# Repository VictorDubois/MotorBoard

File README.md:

Custom PCB, used by KrabiV2.

Drives two brushless motors C610/M2006, controlled with dedicated encoders wheels, and 4 simple transistor outputs.

Driven by a [STM32 NUCLEO-G431KB](https://www.st.com/en/evaluation-tools/nucleo-g431kb.html)

[The code is here](https://github.com/VictorDubois/Motor-board-STM32-CAN)

[Click for online viewer<br/>

](https://kicanvas.org/?repo=https%3A%2F%2Fgithub.com%2FVictorDubois%2FMotorBoard)

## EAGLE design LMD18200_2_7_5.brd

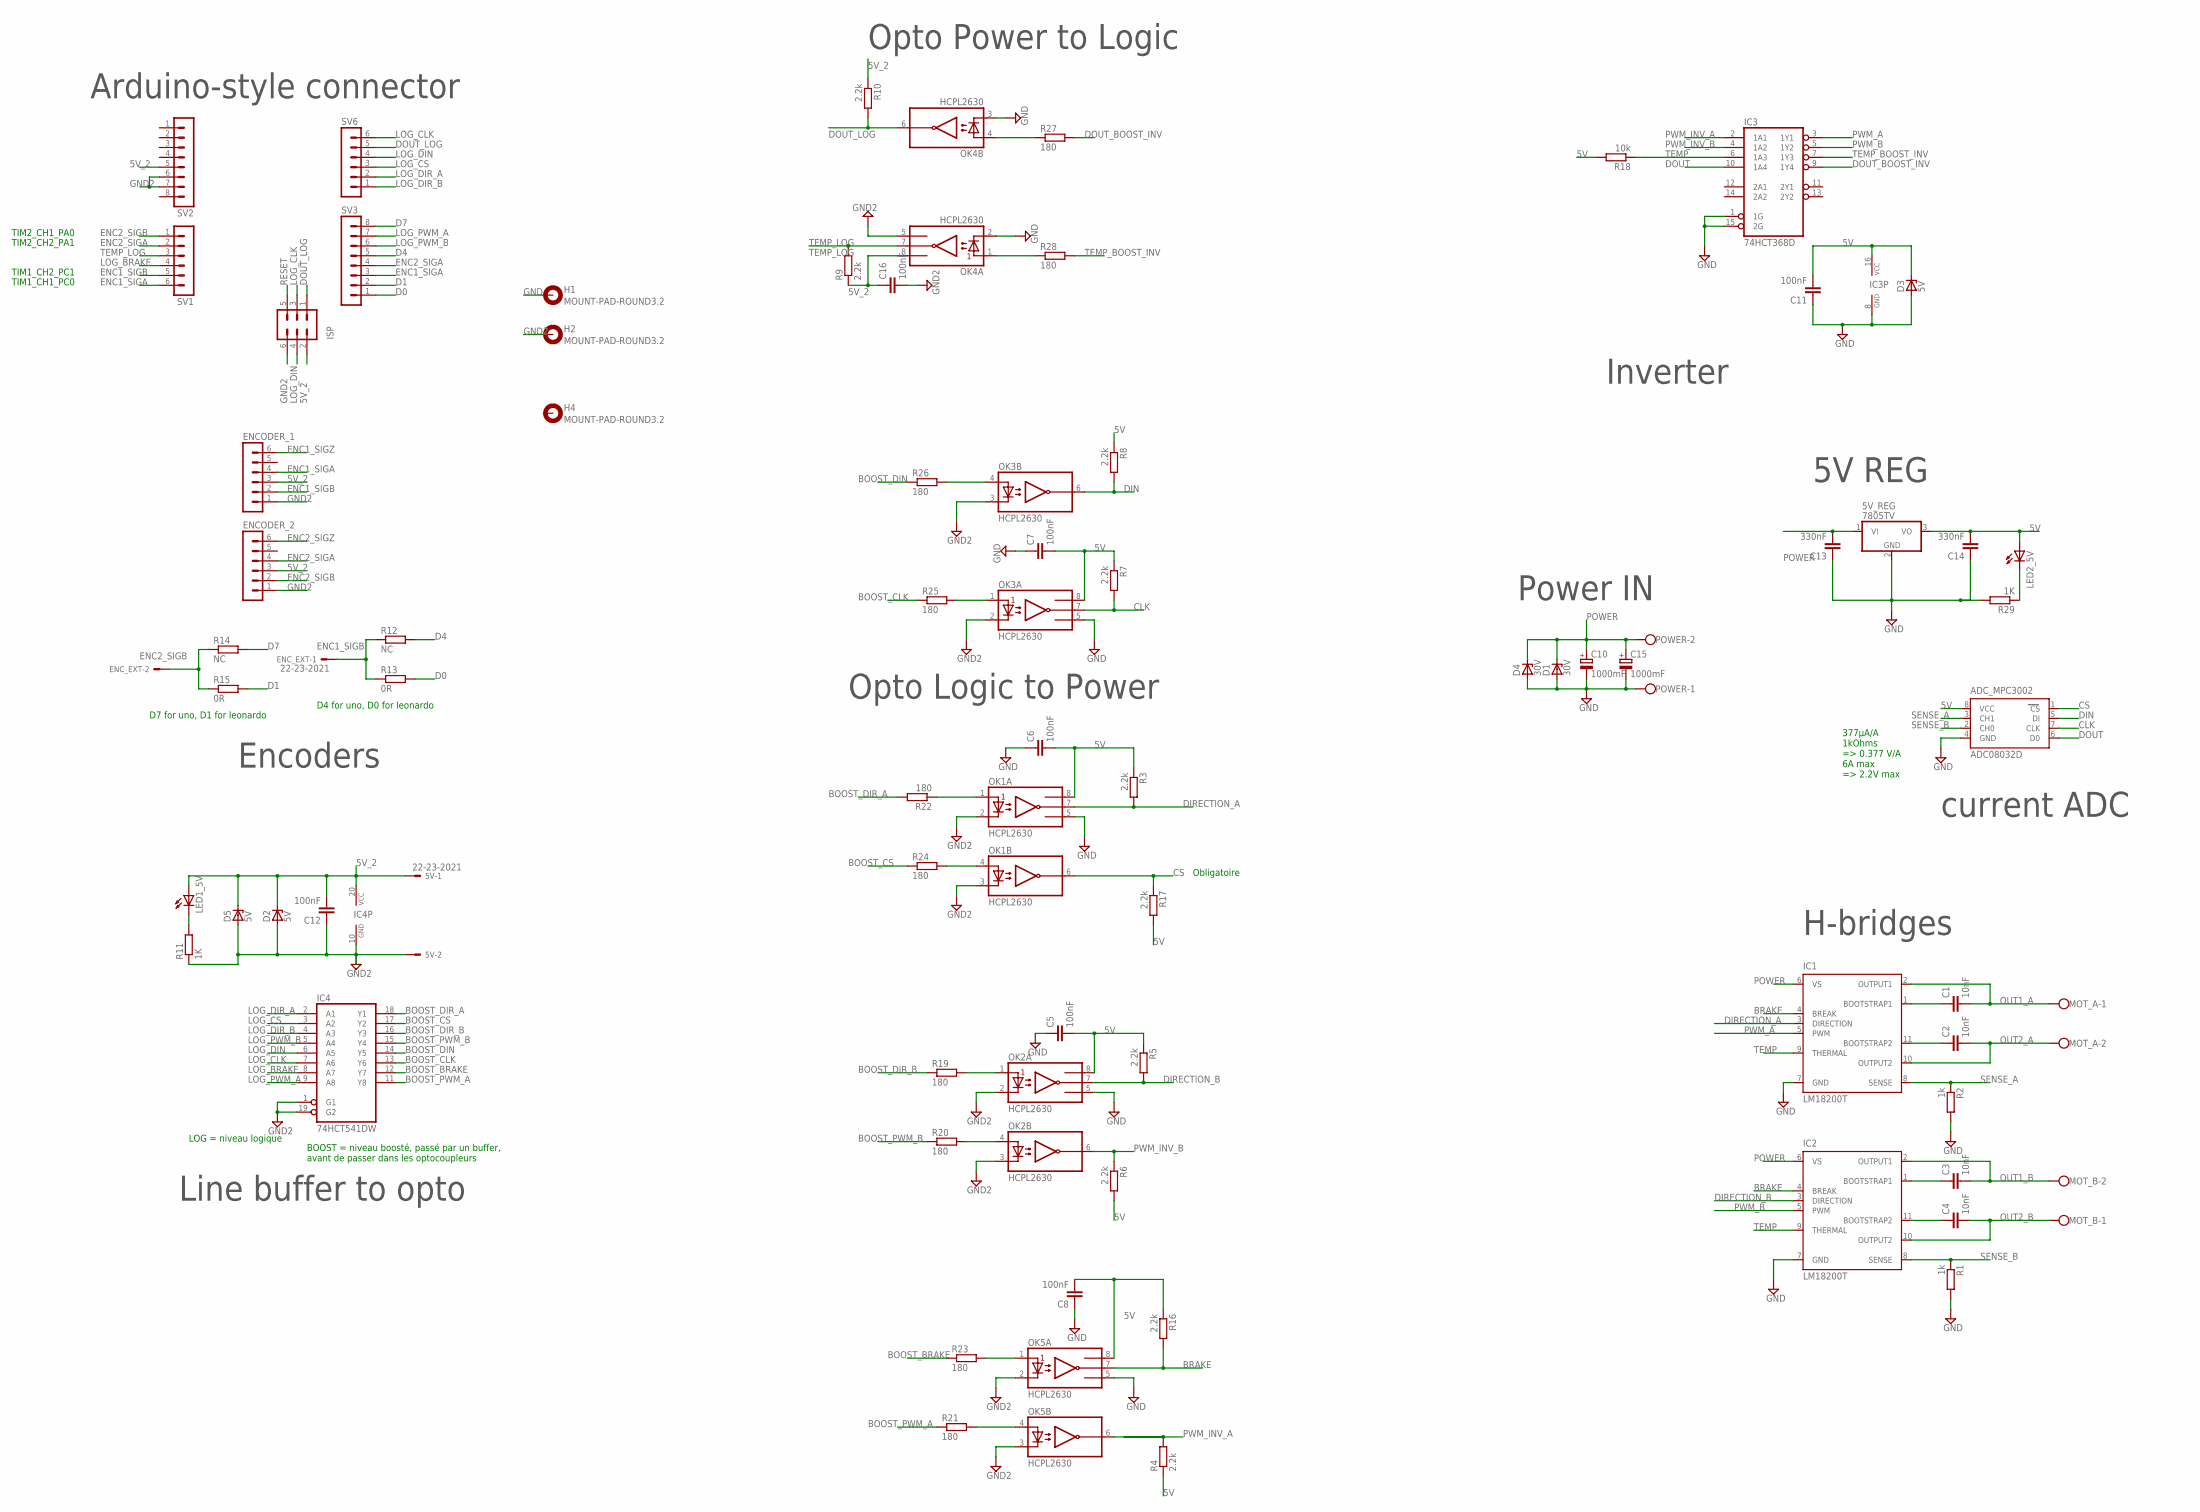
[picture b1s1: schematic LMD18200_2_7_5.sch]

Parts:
5V: 22-23-2021
5V_REG: 7805TV; TO220V
ADC_MPC3002: ADC08032D; SO08
C1, C2, C3, C4: 10nF; C0603
C5, C6, C7, C8, C12, C16: 100nF; C0603
C10, C15: 1000mF; E5-13
C11: 100nF; C0805
C13, C14: 330nF; C0603
D1: 30V; SOD80C
D2: 5V; SOD80C
D3, D5: 5V; DO34Z7
D4: 30V; DO34Z7
ENCODER_1, ENCODER_2: MA06-1
ENC_EXT: 22-23-2021
H1, H2, H4: MOUNT-PAD-ROUND3.2; 3,2-PAD
IC1, IC2: LM18200T; TO-220-11
IC3: 74HCT368D; SO16
IC4: 74HCT541DW; SO20W
ISP: MA03-2
LED1_5V, LED2_5V: LEDSML0805; SML0805
MOT_A: W237-102
MOT_B: W237-102
OK1, OK2, OK3, OK4, OK5: HCPL2630; DIL08
POWER: W237-102
R1, R2: 1k; R0603
R3, R4, R5, R6, R7, R8, R9, R10, R16, R17: 2.2k; R0603
R11, R29: 1K; R0603
R12, R14: NC; R0603
R13, R15: 0R; R0603
R18: 10k; R0603
R19, R20, R21, R22, R23, R24, R25, R26, R27, R28: 180; R0603
SV1, SV6: MA06-1
SV2, SV3: MA08-1

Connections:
5V: 5V_REG.3 (VO), ADC_MPC3002.8 (VCC), C5.2, C6.2, C7.2, C8.2, C11.2, C14.2, D3.C, IC3.16 (VCC), LED2_5V.A, OK1.8 (VCC), OK2.8 (VCC), OK3.8 (VCC), OK5.8 (VCC), R3.1, R4.1, R5.1, R6.2, R7.1, R8.1, R16.1, R17.2, R18.2
5V_2: 5V.1, C12.2, C16.1, D2.C, D5.C, ENCODER_1.3, ENCODER_2.3, IC4.20 (VCC), ISP.2, LED1_5V.A, OK4.8 (VCC), R9.1, R10.1, SV2.5
BOOST_BRAKE: IC4.12 (Y7), R23.1
BOOST_CLK: IC4.13 (Y6), R25.1
BOOST_CS: IC4.17 (Y2), R24.1
BOOST_DIN: IC4.14 (Y5), R26.1
BOOST_DIR_A: IC4.18 (Y1), R22.2
BOOST_DIR_B: IC4.16 (Y3), R19.1
BOOST_OUT1_A: C1.1, IC1.1 (BOOTSTRAP1)
BOOST_OUT1_B: C3.1, IC2.1 (BOOTSTRAP1)
BOOST_OUT2_A: C2.1, IC1.11 (BOOTSTRAP2)
BOOST_OUT2_B: C4.1, IC2.11 (BOOTSTRAP2)
BOOST_PWM_A: IC4.11 (Y8), R21.1
BOOST_PWM_B: IC4.15 (Y4), R20.1
BRAKE: IC1.4 (BREAK), IC2.4 (BREAK), OK5.7 (VO1), R16.2
CLK: ADC_MPC3002.7 (CLK), OK3.7 (VO1), R7.2
CS: ADC_MPC3002.1 (CS), OK1.6 (VO2), R17.1
D0: R13.2, SV3.1
D1: R15.2, SV3.2
D4: R12.2, SV3.5
D7: R14.2, SV3.8
DIN: ADC_MPC3002.5 (DI), OK3.6 (VO2), R8.2
DIRECTION_A: IC1.3 (DIRECTION), OK1.7 (VO1), R3.2
DIRECTION_B: IC2.3 (DIRECTION), OK2.7 (VO1), R5.2
DOUT: ADC_MPC3002.6 (D0), IC3.10 (1A4)
DOUT_BOOST_INV: IC3.9 (1Y4), R27.2
DOUT_LOG: ISP.1, OK4.6 (VO2), R10.2, SV6.5
ENC1_SIGA: ENCODER_1.4, SV1.6, SV3.3
ENC1_SIGB: ENCODER_1.2, ENC_EXT.1, R12.1, R13.1, SV1.5
ENC1_SIGZ: ENCODER_1.6
ENC2_SIGA: ENCODER_2.4, SV1.2, SV3.4
ENC2_SIGB: ENCODER_2.2, ENC_EXT.2, R14.1, R15.1, SV1.1
ENC2_SIGZ: ENCODER_2.6
GND: 5V_REG.2 (GND), ADC_MPC3002.4 (GND), C5.1, C6.1, C7.1, C8.1, C10.-, C11.1, C13.1, C14.1, C15.-, D1.A, D3.A, D4.A, H1.B3,2, IC1.7 (GND), IC2.7 (GND), IC3.1 (1G), IC3.8 (GND), IC3.15 (2G), OK1.5 (GND), OK2.5 (GND), OK3.5 (GND), OK4.2 (C1), OK4.3 (C2), OK5.5 (GND), POWER.1, R1.2, R2.2, R29.2
GND2: 5V.2, C12.1, C16.2, D2.A, D5.A, ENCODER_1.1, ENCODER_2.1, H2.B3,2, IC4.1 (G1), IC4.10 (GND), IC4.19 (G2), ISP.6, OK1.2 (C1), OK1.3 (C2), OK2.2 (C1), OK2.3 (C2), OK3.2 (C1), OK3.3 (C2), OK4.5 (GND), OK5.2 (C1), OK5.3 (C2), R11.1, SV2.6, SV2.7
LED1_SIG: LED1_5V.C, R11.2
LED2_5V_SIG: LED2_5V.C, R29.1
LOG_BRAKE: IC4.8 (A7), SV1.4
LOG_CLK: IC4.7 (A6), ISP.3, SV6.6
LOG_CS: IC4.3 (A2), SV6.3
LOG_DIN: IC4.6 (A5), ISP.4, SV6.4
LOG_DIR_A: IC4.2 (A1), SV6.2
LOG_DIR_B: IC4.4 (A3), SV6.1
LOG_PWM_A: IC4.9 (A8), SV3.7
LOG_PWM_B: IC4.5 (A4), SV3.6
OUT1_A: C1.2, IC1.2 (OUTPUT1), MOT_A.1
OUT1_B: C3.2, IC2.2 (OUTPUT1), MOT_B.2
OUT2_A: C2.2, IC1.10 (OUTPUT2), MOT_A.2
OUT2_B: C4.2, IC2.10 (OUTPUT2), MOT_B.1
POWER: 5V_REG.1 (VI), C10.+, C13.2, C15.+, D1.C, D4.C, IC1.6 (VS), IC2.6 (VS), POWER.2
PWM_A: IC1.5 (PWM), IC3.3 (1Y1)
PWM_B: IC2.5 (PWM), IC3.5 (1Y2)
PWM_INV_A: IC3.2 (1A1), OK5.6 (VO2), R4.2
PWM_INV_B: IC3.4 (1A2), OK2.6 (VO2), R6.1
RESET: ISP.5
R_BOOST_BRAKE: OK5.1 (A1), R23.2
R_BOOST_CLK: OK3.1 (A1), R25.2
R_BOOST_CS: OK1.4 (A2), R24.2
R_BOOST_DIN: OK3.4 (A2), R26.2
R_BOOST_DIR_A: OK1.1 (A1), R22.1
R_BOOST_DIR_B: OK2.1 (A1), R19.2
R_BOOST_PWM_A: OK5.4 (A2), R21.2
R_BOOST_PWM_B: OK2.4 (A2), R20.2
R_DOUT_BOOST_INV: OK4.4 (A2), R27.1
R_TEMP_BOOST_INV: OK4.1 (A1), R28.1
SENSE_A: ADC_MPC3002.3 (CH1), IC1.8 (SENSE), R2.1
SENSE_B: ADC_MPC3002.2 (CH0), IC2.8 (SENSE), R1.1
TEMP: IC1.9 (THERMAL), IC2.9 (THERMAL), IC3.6 (1A3), R18.1
TEMP_BOOST_INV: IC3.7 (1Y3), R28.2
TEMP_LOG: OK4.7 (VO1), R9.2, SV1.3

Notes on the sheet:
D4 for uno, D0 for leonardo
D7 for uno, D1 for leonardo
LOG = niveau logique
BOOST = niveau boosté, passé par un buffer, avant de passer dans les optocoupleurs
Obligatoire
H-bridges
current ADC
TIM1_CH1_PC0
TIM1_CH2_PC1
TIM2_CH2_PA1
TIM2_CH1_PA0
377µA/A 1kOhms => 0.377 V/A 6A max => 2.2V max
5V REG
Power IN
Inverter
Opto Power to Logic
Opto Logic to Power
Arduino-style connector
Encoders
Line buffer to opto

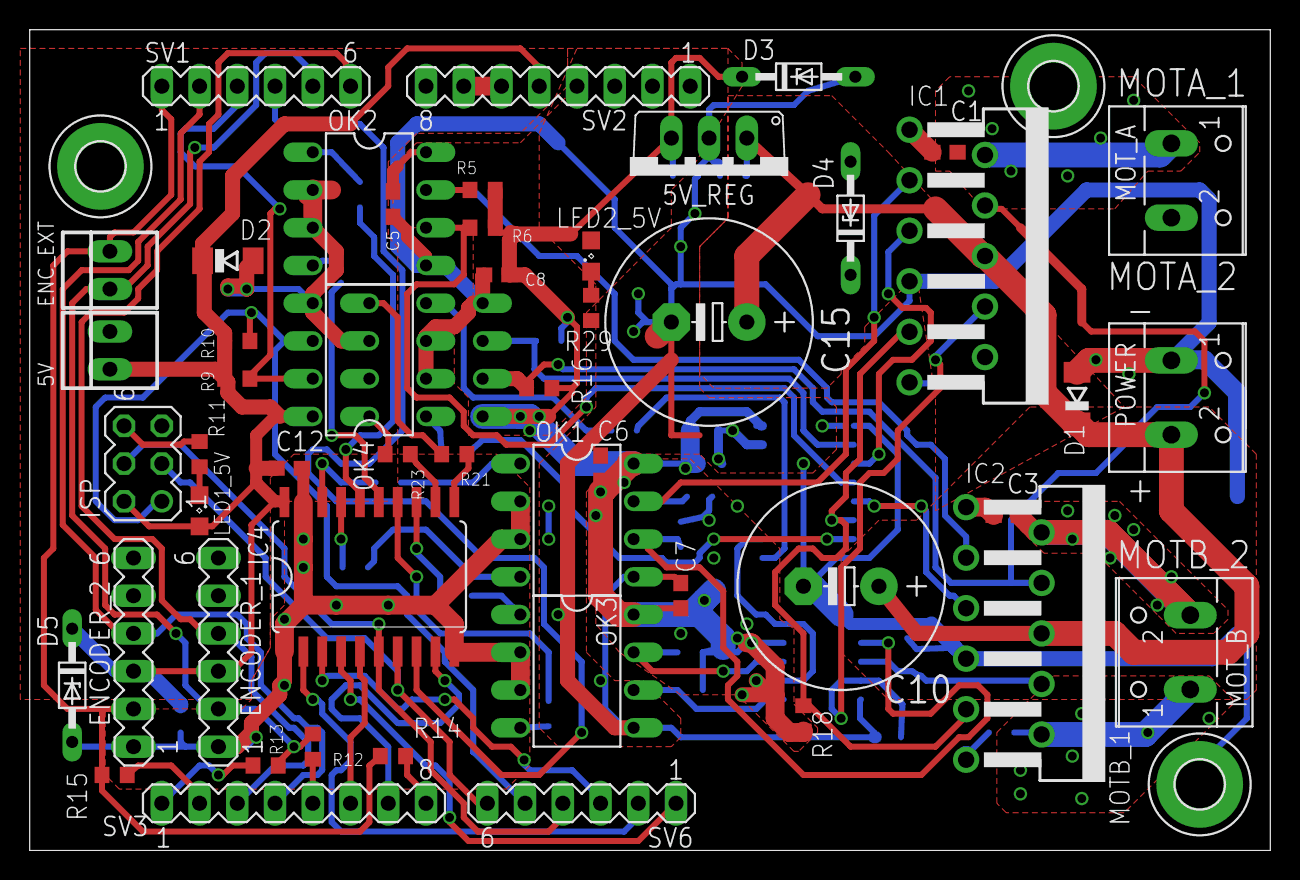
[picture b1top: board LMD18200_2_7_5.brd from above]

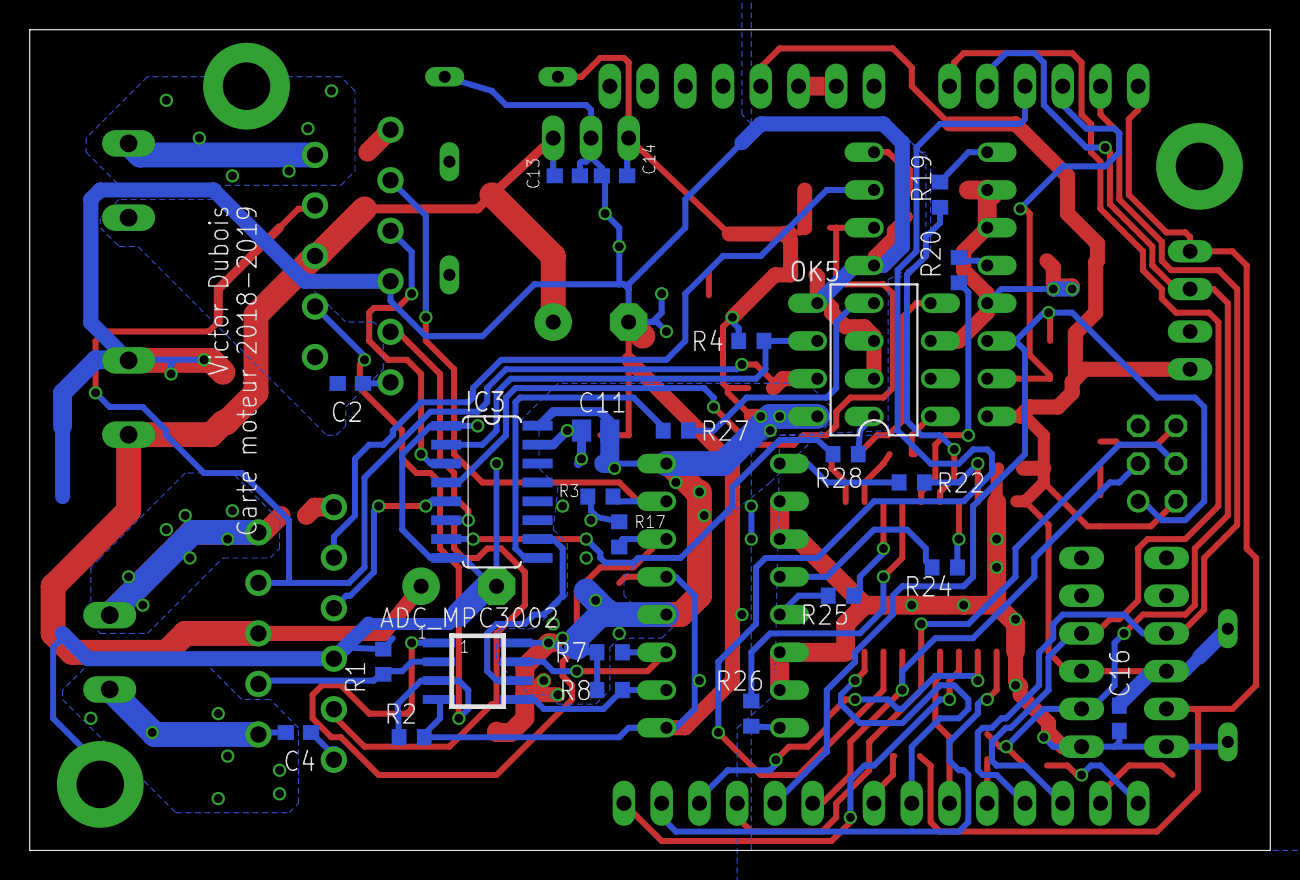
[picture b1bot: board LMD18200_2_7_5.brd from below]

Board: 2 copper layers, 83.5 x 55.2 mm, 77 parts (24 on the bottom side), 67 nets.

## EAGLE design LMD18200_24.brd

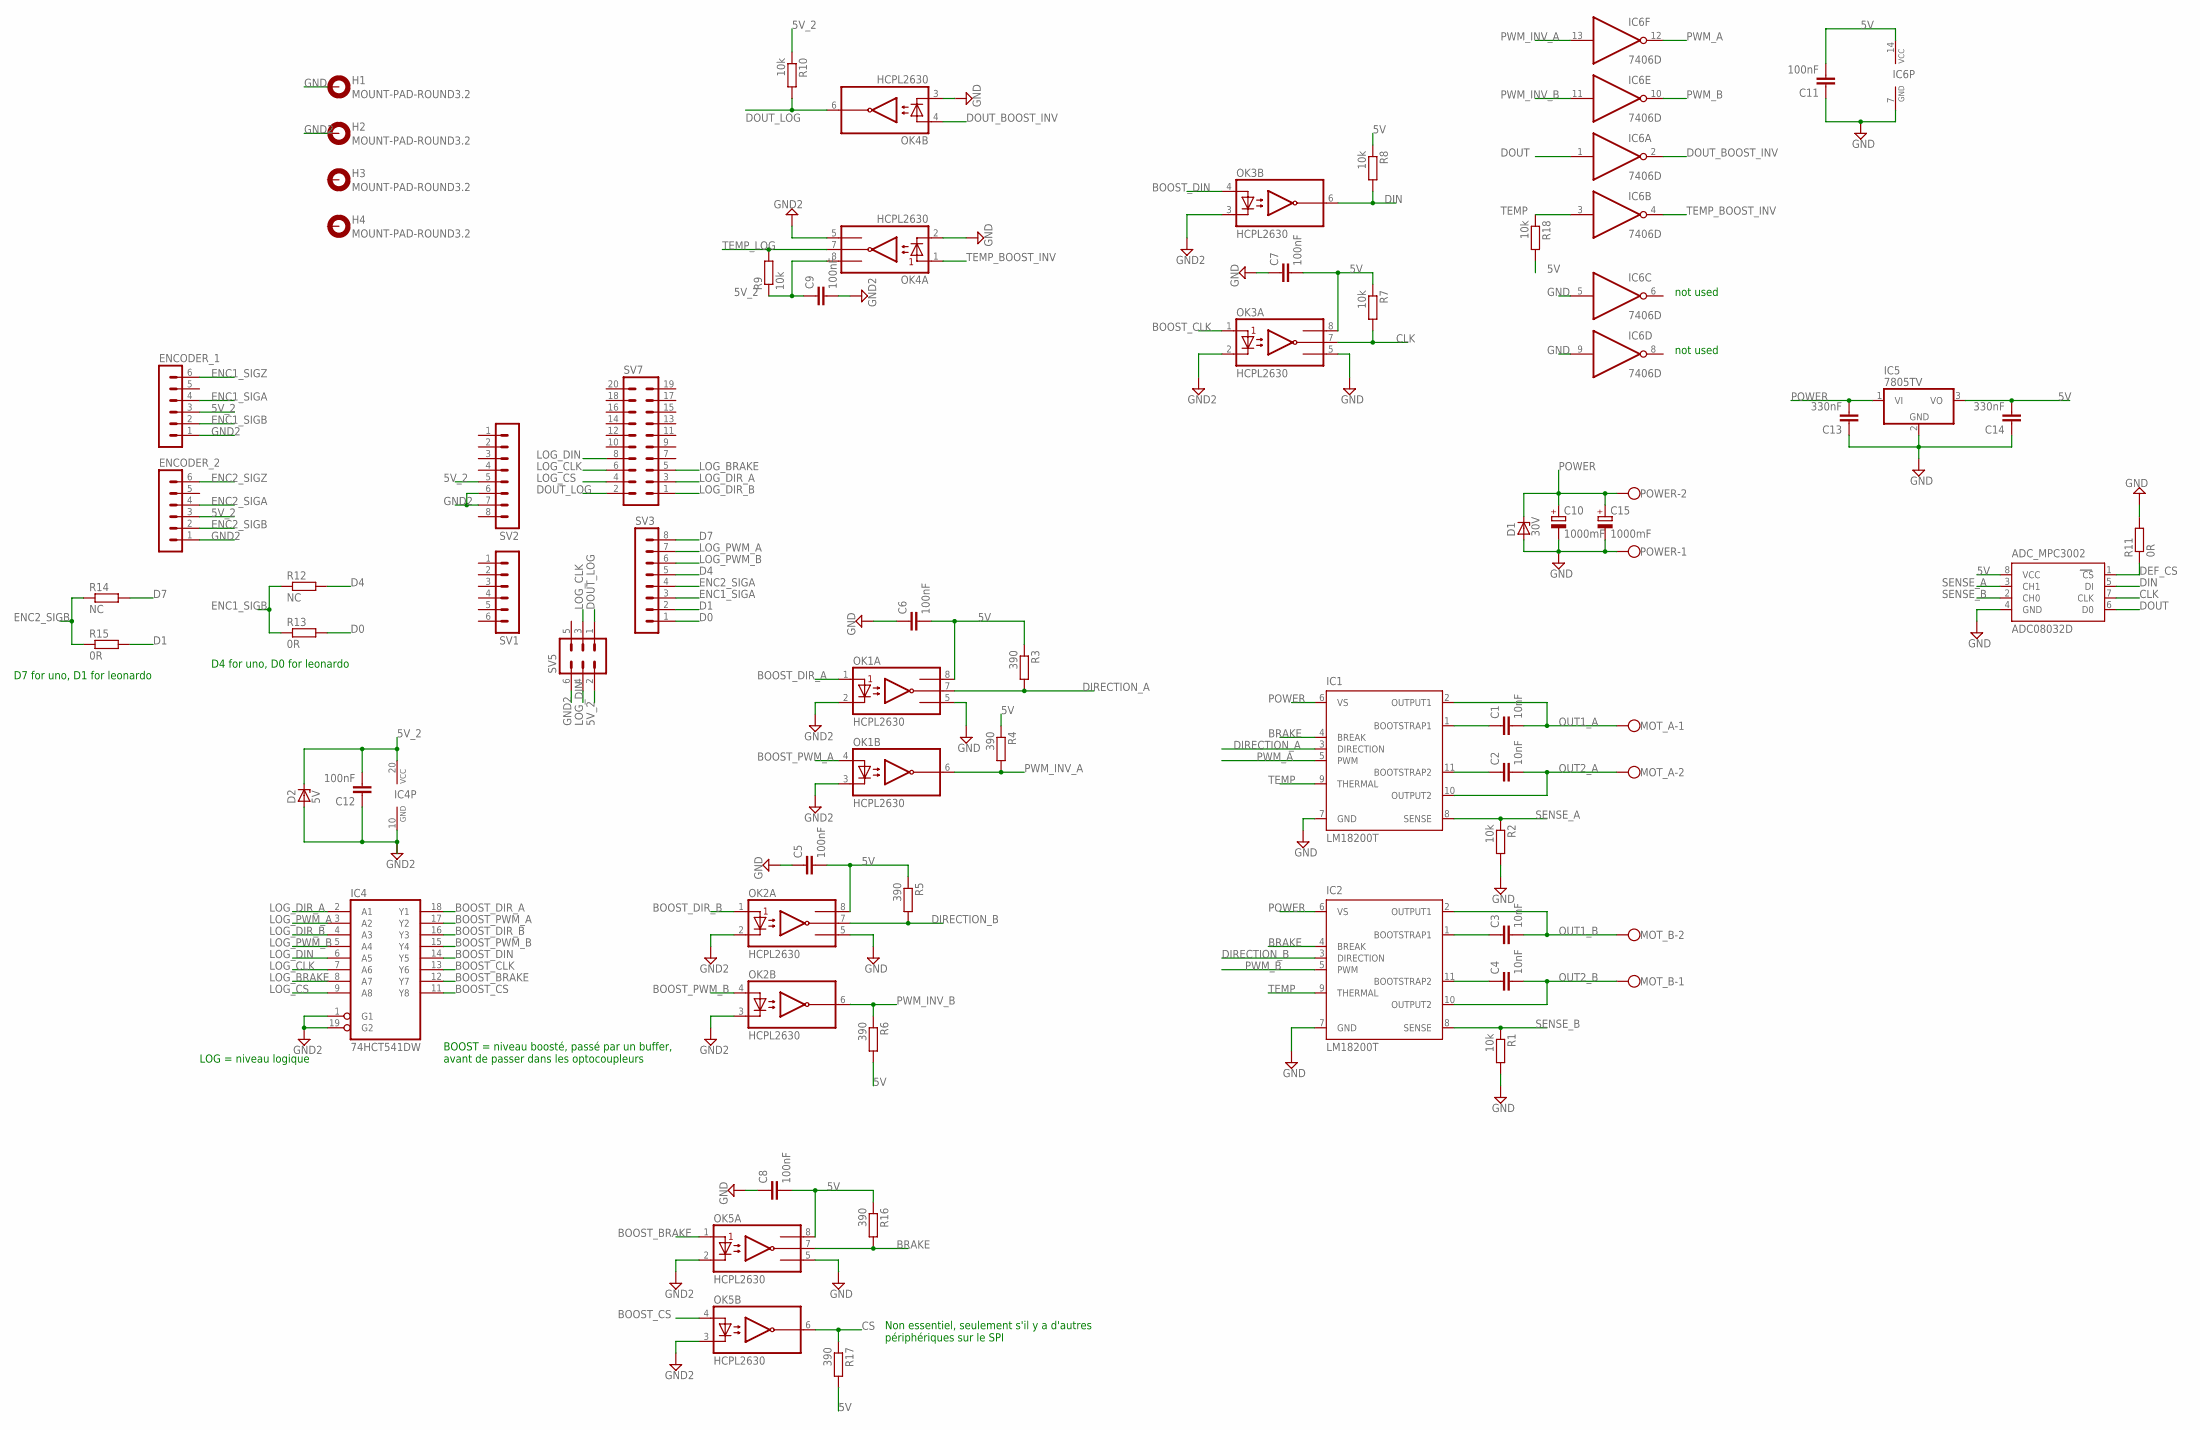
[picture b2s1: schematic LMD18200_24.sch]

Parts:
ADC_MPC3002: ADC08032D; SO08
C1, C2, C3, C4: 10nF; C2.5-2
C5, C6, C7, C8, C9, C12: 100nF; C2.5-2
C10, C15: 1000mF; E5-13
C11: 100nF; C0805
C13, C14: 330nF; C2.5-2
D1: 30V; SOD80C
D2: 5V; SOD80C
ENCODER_1, ENCODER_2: MA06-1
H1, H2, H3, H4: MOUNT-PAD-ROUND3.2; 3,2-PAD
IC1, IC2: LM18200T; TO-220-11
IC4: 74HCT541DW; SO20W
IC5: 7805TV; TO220V
IC6: 7406D; SO14
MOT_A: W237-102
MOT_B: W237-102
OK1, OK2, OK3, OK4, OK5: HCPL2630; DIL08
POWER: W237-102
R1, R2, R7, R8, R9, R10, R18: 10k; R0805
R3, R4, R5, R6, R16, R17: 390; R0805
R11, R13, R15: 0R; R0805
R12, R14: NC; R0805
SV1: MA06-1
SV2, SV3: MA08-1
SV5: MA03-2
SV7: MA10-2

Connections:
5V: ADC_MPC3002.8 (VCC), C5.2, C6.2, C7.2, C8.2, C11.2, C14.2, IC5.3 (VO), IC6.14 (VCC), OK1.8 (VCC), OK2.8 (VCC), OK3.8 (VCC), OK5.8 (VCC), R3.1, R4.1, R5.1, R6.2, R7.1, R8.1, R16.1, R17.2, R18.2
5V_2: C9.1, C12.2, D2.C, ENCODER_1.3, ENCODER_2.3, IC4.20 (VCC), OK4.8 (VCC), R9.1, R10.1, SV2.5, SV5.2
BOOST_BRAKE: IC4.12 (Y7), OK5.1 (A1)
BOOST_CLK: IC4.13 (Y6), OK3.1 (A1)
BOOST_CS: IC4.11 (Y8), OK5.4 (A2)
BOOST_DIN: IC4.14 (Y5), OK3.4 (A2)
BOOST_DIR_A: IC4.18 (Y1), OK1.1 (A1)
BOOST_DIR_B: IC4.16 (Y3), OK2.1 (A1)
BOOST_PWM_A: IC4.17 (Y2), OK1.4 (A2)
BOOST_PWM_B: IC4.15 (Y4), OK2.4 (A2)
BRAKE: IC1.4 (BREAK), IC2.4 (BREAK), OK5.7 (VO1), R16.2
CLK: ADC_MPC3002.7 (CLK), OK3.7 (VO1), R7.2
CS: OK5.6 (VO2), R17.1
D0: R13.2, SV3.1
D1: R15.2, SV3.2
D4: R12.2, SV3.5
D7: R14.2, SV3.8
DEF_CS: ADC_MPC3002.1 (CS), R11.1
DIN: ADC_MPC3002.5 (DI), OK3.6 (VO2), R8.2
DIRECTION_A: IC1.3 (DIRECTION), OK1.7 (VO1), R3.2
DIRECTION_B: IC2.3 (DIRECTION), OK2.7 (VO1), R5.2
DOUT: ADC_MPC3002.6 (D0), IC6.1 (I)
DOUT_BOOST_INV: IC6.2 (O), OK4.4 (A2)
DOUT_LOG: OK4.6 (VO2), R10.2, SV5.1, SV7.2
ENC1_SIGA: ENCODER_1.4, SV3.3
ENC1_SIGB: ENCODER_1.2, R12.1, R13.1
ENC1_SIGZ: ENCODER_1.6
ENC2_SIGA: ENCODER_2.4, SV3.4
ENC2_SIGB: ENCODER_2.2, R14.1, R15.1
ENC2_SIGZ: ENCODER_2.6
GND: ADC_MPC3002.4 (GND), C5.1, C6.1, C7.1, C8.1, C10.-, C11.1, C13.1, C14.1, C15.-, D1.A, H1.B3,2, IC1.7 (GND), IC2.7 (GND), IC5.2 (GND), IC6.5 (I), IC6.7 (GND), IC6.9 (I), OK1.5 (GND), OK2.5 (GND), OK3.5 (GND), OK4.2 (C1), OK4.3 (C2), OK5.5 (GND), POWER.1, R1.2, R2.2, R11.2
GND2: C9.2, C12.1, D2.A, ENCODER_1.1, ENCODER_2.1, H2.B3,2, IC4.1 (G1), IC4.10 (GND), IC4.19 (G2), OK1.2 (C1), OK1.3 (C2), OK2.2 (C1), OK2.3 (C2), OK3.2 (C1), OK3.3 (C2), OK4.5 (GND), OK5.2 (C1), OK5.3 (C2), SV2.6, SV2.7, SV5.6
LOG_BRAKE: IC4.8 (A7), SV7.5
LOG_CLK: IC4.7 (A6), SV5.3, SV7.6
LOG_CS: IC4.9 (A8), SV7.4
LOG_DIN: IC4.6 (A5), SV5.4, SV7.8
LOG_DIR_A: IC4.2 (A1), SV7.3
LOG_DIR_B: IC4.4 (A3), SV7.1
LOG_PWM_A: IC4.3 (A2), SV3.7
LOG_PWM_B: IC4.5 (A4), SV3.6
unnamed: C1.1, IC1.1 (BOOTSTRAP1)
unnamed: C2.1, IC1.11 (BOOTSTRAP2)
unnamed: C3.1, IC2.1 (BOOTSTRAP1)
unnamed: C4.1, IC2.11 (BOOTSTRAP2)
OUT1_A: C1.2, IC1.2 (OUTPUT1), MOT_A.1
OUT1_B: C3.2, IC2.2 (OUTPUT1), MOT_B.2
OUT2_A: C2.2, IC1.10 (OUTPUT2), MOT_A.2
OUT2_B: C4.2, IC2.10 (OUTPUT2), MOT_B.1
POWER: C10.+, C13.2, C15.+, D1.C, IC1.6 (VS), IC2.6 (VS), IC5.1 (VI), POWER.2
PWM_A: IC1.5 (PWM), IC6.12 (O)
PWM_B: IC2.5 (PWM), IC6.10 (O)
PWM_INV_A: IC6.13 (I), OK1.6 (VO2), R4.2
PWM_INV_B: IC6.11 (I), OK2.6 (VO2), R6.1
SENSE_A: ADC_MPC3002.3 (CH1), IC1.8 (SENSE), R2.1
SENSE_B: ADC_MPC3002.2 (CH0), IC2.8 (SENSE), R1.1
TEMP: IC1.9 (THERMAL), IC2.9 (THERMAL), IC6.3 (I), R18.1
TEMP_BOOST_INV: IC6.4 (O), OK4.1 (A1)
TEMP_LOG: OK4.7 (VO1), R9.2

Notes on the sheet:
D4 for uno, D0 for leonardo
D7 for uno, D1 for leonardo
LOG = niveau logique
BOOST = niveau boosté, passé par un buffer, avant de passer dans les optocoupleurs
Non essentiel, seulement s'il y a d'autres périphériques sur le SPI
not used

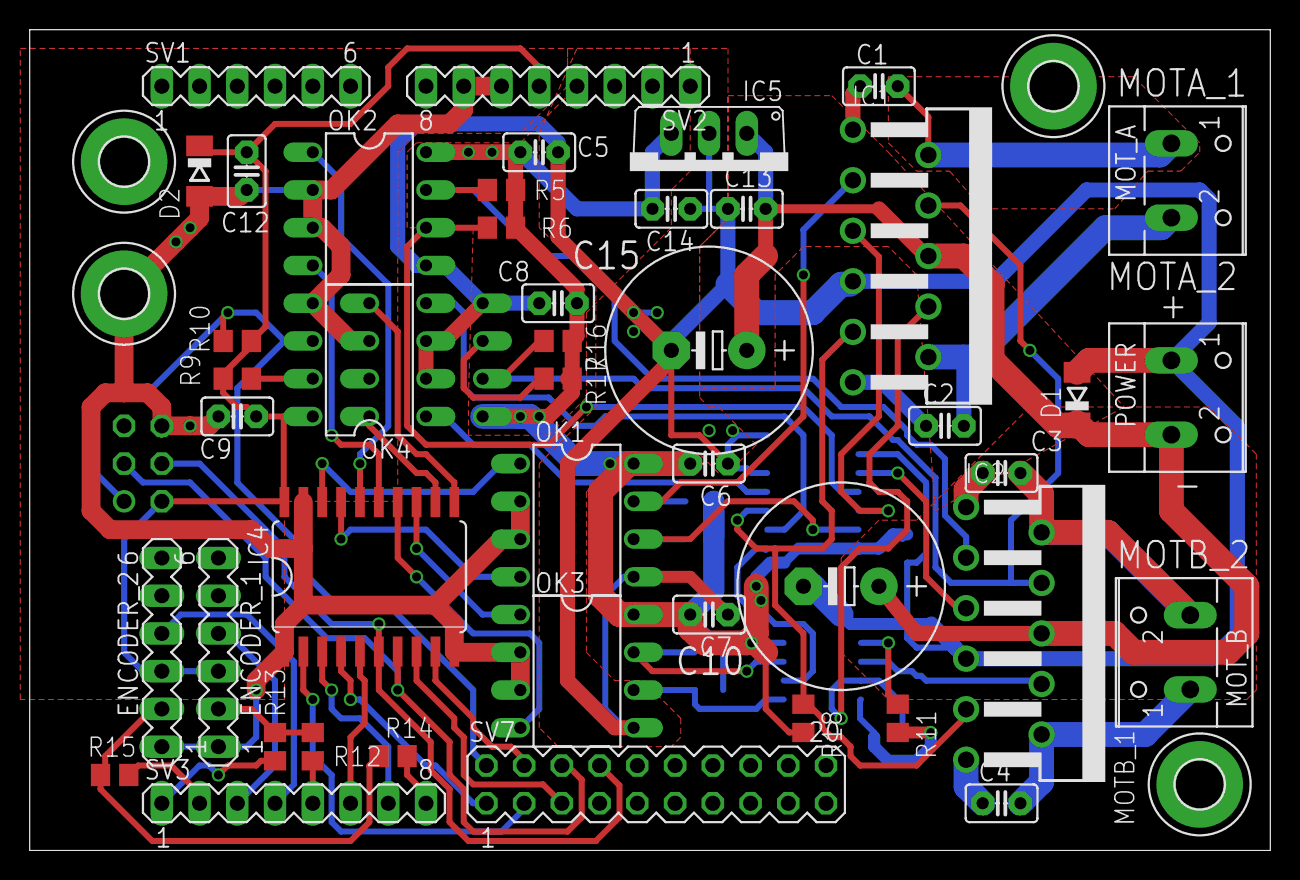
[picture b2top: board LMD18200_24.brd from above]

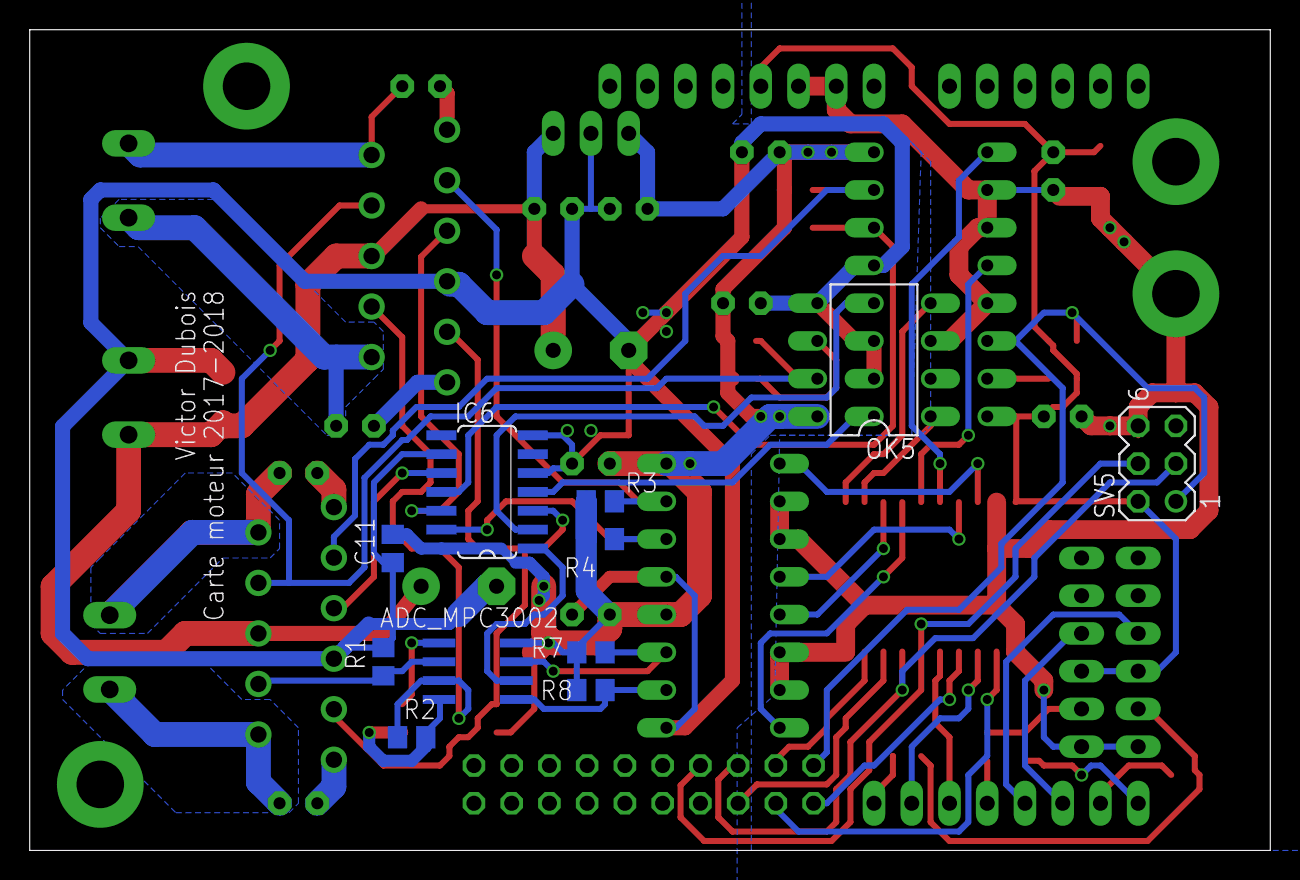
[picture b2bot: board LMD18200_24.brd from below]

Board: 2 copper layers, 83.5 x 55.2 mm, 60 parts (11 on the bottom side), 56 nets.

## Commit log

2018-03-22 close #1 creation
2022-08-28 second board version
2022-10-08 add readme
2025-08-15 Add option 12V Elec + add missing brake pullups
2025-08-15 add choice between 12V power and 24V power
2026-01-18 remove DC motors + schematic labels
2026-01-18 basic routing of C610 connectors
2026-01-18 small tuning
2026-01-18 serigraphy
2026-01-21 move capacitors for easier access to main bus connectors + add 24V flood fill
2026-02-05 various updates
2026-02-05 remove pressure measure, add voltage measure, re-route
2026-02-06 change capacitor references to support >25V
2026-05-21 Initialize README with project details and links
    Added project description and links for motor board control.
2026-06-20 fix transistor by adding a correct free-wheeling diode
2026-06-20 update to Kicad 10 + fix warnings
2026-06-20 bigger jumper resistors
2026-06-20 improve GND routing
2026-06-20 Clarify PCB usage for Krabi V1 and V2
    Updated README to specify Krabi V1 and V2 PCB usage.
2026-06-20 fix readme
